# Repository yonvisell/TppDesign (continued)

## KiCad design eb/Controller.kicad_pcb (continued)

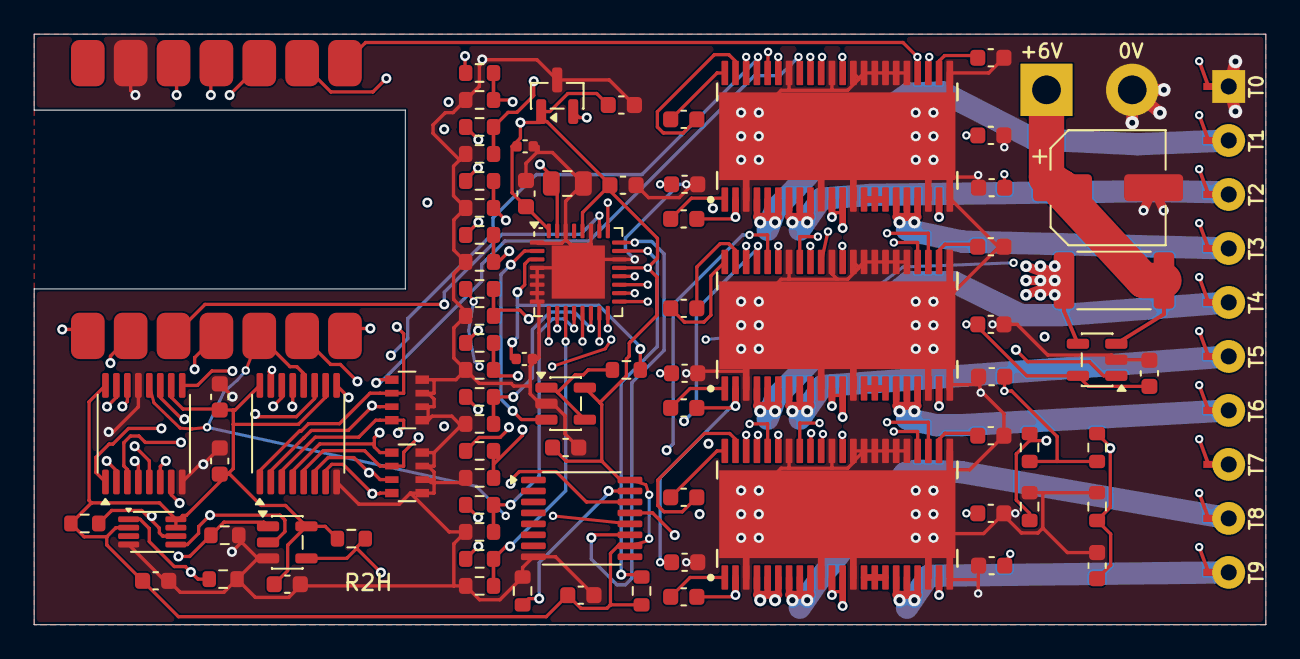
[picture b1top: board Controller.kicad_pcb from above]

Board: 4 copper layers, 73.0 x 35.0 mm, 82 parts (0 on the bottom side), 85 nets.

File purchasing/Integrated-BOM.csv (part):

group,ref,item,supplier,identity,purchase_unit,low,high,first,repeat,second,existing_eb,basis,source,first_low,first_high,repeat_low,repeat_high,second_low,second_high,existing_eb_low,existing_eb_high
Display / tooling,H01,"Four-layer display board, 0.80 mm FR-4",JLCPCB,R2J display PCB Gerbers and drill files,5 bare boards,35.0,115.0,1,0.2,0,1,"Allowance for five boards and precision routing on a removable rail panel. Confirm total aperture contour position to copper and datums, inside radius and inner 1 oz layers. One of five bare display boards.",https://jlcpcb.com/capabilities/pcb-capabilities/,35.0,115.0,7.0,23.0,0.0,0.0,35.0,115.0
Display / tooling,H02,Bare annealed 0.127 mm C110 copper,Trinity Brand Industries,6CPR12-5,"1 sheet, 6 × 12 in",14.96,14.96,1,0.041666666666666664,0,1,"Catalog unit, ASTM B152. Hand-trim identical 10 mm-wide tab outlines and perforate the upper foil with nine 0.600 mm holes. 24 copper pairs per sheet after offcuts and witnesses.",https://www.trinitybrand.com/item/copper/copper-1/6cpr12-5,14.96,14.96,0.6233333333333333,0.6233333333333333,0.0,0.0,14.96,14.96
Display / tooling,H03a,Plain 0.0254 mm Kapton HN dielectric,CS Hyde,18-1F-12x12,"1 sheet, 12 × 12 in",10.9,10.9,1,0.02,0,1,Catalog unit. L02/L03 and L11/L12 protect the two tab roots. Cut three 0.60 × 1.48 mm wire-tail retainers from upper-liner offcuts. 50 display sets per plain HN sheet. Two blanks per set; K1–K3 use offcuts.,https://catalog.cshyde.com/viewitems/films/kapton-polyimide-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,10.9,10.9,0.218,0.218,0.0,0.0,10.9,10.9
Display / tooling,H03c,Plain 0.1016 mm polyimide spacer sheet,CS Hyde,18-4F-P,"1 ft, 20 in wide",50.87,50.87,1,0.00625,0,1,Catalog unit. Use solid 4 mil polyimide. Measure installed spacer and free gasket thickness. 160 compression spacers per 20 x 12 inch PI sheet.,https://cshyde.com/item/films/thick-polyimide-film/4mil-poly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,50.87,50.87,0.3179375,0.3179375,0.0,0.0,50.87,50.87
Display / tooling,H03d,"Acrylic transfer adhesive, two release liners",CS Hyde / 3M,3M-467MP-12x12,"1 sheet, 12 × 12 in",5.76,5.76,1,0.0625,0,1,"Catalog unit, 0.0584 mm dry. Prelaminate PI before blade cutting and retain the release liner. Bore L11/L12 to 0.425 mm after registering to L13. 16 sets of six transfer adhesive patterns per sheet.",https://cshyde.com/item/3m-products/3m-adhesive-transfer-tap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,5.76,5.76,0.36,0.36,0.0,0.0,5.76,5.76
Display / tooling,H04,Rigid 0.40 mm bare FR-4 aperture cap,JLCPCB,R2J aperture cap Gerber and drill,5 bare caps,12.0,55.0,1,0.2,0,1,"Allowance. Manual review for thin FR-4 with no metal, solder mask or marks on the finished article. Confirm plotted apertures, tolerance and bonding surfaces. One of five aperture caps.",https://jlcpcb.com/capabilities/pcb-capabilities/,12.0,55.0,2.4000000000000004,11.0,0.0,0.0,12.0,55.0
Display / tooling,H05,"Silicone/acrylic face bond, 0.14 mm",Guardia Industries / 3M,"3M 9731 cut sheet, listing 196227895184","1 sheet, 10 × 10 in",12.0,12.0,1,0.016666666666666666,0,1,"Marketplace cut sheet. Verify lot, age, liners and witness adhesion on the actual cap and silicone. Full-roll alternative adds $230 before tax. 60 face bonds per 10 x 10 inch sheet after witnesses.",https://www.ebay.com/itm/196227895184,12.0,12.0,0.2,0.2,0.0,0.0,12.0,12.0
Display / tooling,H06,Plain 0.010 in 35A silicone,McMaster-Carr,86435K31,"1 sheet, 12 × 12 in",25.0,70.0,1,0.02,0,1,SKU and size in catalog. Account price and ship date unconfirmed. Cut both bare silicone parts in the lab. 50 gasket and diaphragm pairs per sheet after trials.,https://www.mcmaster.com/products/rubber/color~cream/,25.0,70.0,0.5,1.4000000000000001,0.0,0.0,25.0,70.0
Display / tooling,H07,Bare Ni80Cr20 AWG 48 heater wire,KP Wire,N80_500_SPOOL_48g,"1 spool, 500 ft",25.2,25.2,1,0.004330708661417323,0,1,Selected gauge listed as purchasable. Allow 55 mm per strand cut. Four-strand build uses at most twelve 55 mm cuts.,https://kpwire.com/remote/v1/product-attributes/133?attribut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,25.2,25.2,0.10913385826771653,0.10913385826771653,0.0,0.0,25.2,25.2
Display / tooling,H08,"26 AWG, 19/38 thin-wall PTFE tap leads",WireMasters,M16878/6-BDE-9,24 ft cut length,9.6,9.6,1,0.4101049868766404,0,1,Unit price $0.40/ft. The lot supplies two ten-lead harnesses and 1.32 m total cutting margin. Identify both ends before assembly. 3.0 m of leads used from the 24 ft first purchase.,https://www.wiremasters.com/product/m16878-6-bde-9,9.6,9.6,3.9370078740157473,3.9370078740157473,0.0,0.0,9.6,9.6
Display / tooling,H09a,Winding-tool base PCB,JLCPCB,R2J winding base fabrication CAM,5 bare boards,5.0,25.0,1,0,0,1,Bare-board and relief machining allowance. Reusable base PCB.,https://jlcpcb.com/capabilities/pcb-capabilities/,5.0,25.0,0.0,0.0,0.0,0.0,5.0,25.0
Display / tooling,H09b,Adjustable winding frame PCB,JLCPCB,R2J winding frame fabrication CAM,5 bare boards,8.0,35.0,1,0,0,1,"Allowance for bare FR-4 plate with 24 guides, two clamp slots and a display clearance window. Reusable frame PCB.",https://jlcpcb.com/capabilities/pcb-capabilities/,8.0,35.0,0.0,0.0,0.0,0.0,8.0,35.0
Display / tooling,H10,Straight 0.30 mm steel winding-guide stock,Vermont Gage,"112200300, Class ZZ minus, 2 in","4 blanks, 2 in each",21.0,21.0,1,0,0,1,Maker catalog $5.25 per blank. Four 50.8 mm lengths yield 28 nominal 6 mm sections allowing cutting kerf. Confirm seller stock. Winding guides stay with the tooling.,https://vermontgage.com/assets/catalogs/2025-VG-Catalog/f37c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,21.0,21.0,0.0,0.0,0.0,0.0,21.0,21.0
Display / tooling,H11,Straight 0.45 mm steel registration stock,Vermont Gage,"112400450, Class ZZ minus, 2 in","1 blank, 2 in",5.25,5.25,1,0,0,1,Maker catalog $5.25 per blank. One 50.8 mm length yields seven nominal 6 mm sections allowing cutting kerf. Confirm seller stock. Registration pins stay with the tooling.,https://vermontgage.com/assets/catalogs/2025-VG-Catalog/f37c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,5.25,5.25,0.0,0.0,0.0,0.0,5.25,5.25
Display / tooling,H12,"M2 clamps, caul and shop consumables",Owner shop,"M2 hardware, caul blank, epoxy, strain relief, labels, blades and bits",1 shop lot,7.0,30.0,1,0.1,0,1,"Shop allowance for a supported precision drill or punch, sacrificial backer, M2 clamps and supplies. Assumes existing microscope, adjustable stage, solder tools and Rayjet. Optional thermal-joint tooling and qualification are outside the flat-head budget. Estimated 10% repeat usage for labels and consumables. M2 hardware is reused.",Shop allowance,7.0,30.0,0.7000000000000001,3.0,0.0,0.0,7.0,30.0
Driver components,A1,XIAO ESP32-C6,Seeed via JLCPCB,113991254 / C27675191,1 component,7.6389,7.6389,2,1,0,0,1 per board. Two boards plus purchase minimum or attrition. Catalog stock at the saved lookup: 96.,https://jlcpcb.com/partdetail/C27675191,15.2778,15.2778,7.6389,7.6389,0.0,0.0,0.0,0.0
Driver components,U6,74LVC1G74,Texas Instruments via JLCPCB,SN74LVC1G74DCUR / C70285,1 component,0.4991,0.4991,5,1,0,0,1 per board. Two boards plus purchase minimum or attrition. Catalog stock at the saved lookup: 3874.,https://jlcpcb.com/partdetail/C70285,2.4955,2.4955,0.4991,0.4991,0.0,0.0,0.0,0.0
Driver components,U7,74LVC1G00,Texas Instruments via JLCPCB,SN74LVC1G00DBVR / C7826,1 component,0.2158,0.2158,6,1,0,0,1 per board. Two boards plus purchase minimum or attrition. Catalog stock at the saved lookup: 13788.,https://jlcpcb.com/partdetail/C7826,1.2948,1.2948,0.2158,0.2158,0.0,0.0,0.0,0.0
Driver components,"C24,C25,C22,C23,C2,C4,C8,C10,C14,C16,C26,C28,C34",100nF,YAGEO via JLCPCB,CC0603KRX7R9BB104 / C14663,1 component,0.0064,0.0064,41,13,0,0,13 per board. Two boards plus purchase minimum or attrition. Catalog stock at the saved lookup: 53069809.,https://jlcpcb.com/partdetail/C14663,0.2624,0.2624,0.08320000000000001,0.08320000000000001,0.0,0.0,0.0,0.0
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
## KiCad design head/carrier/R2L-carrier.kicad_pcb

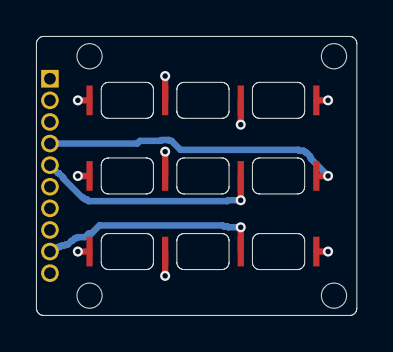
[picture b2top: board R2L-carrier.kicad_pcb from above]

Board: 4 copper layers, 17.8 x 15.5 mm, 17 parts (0 on the bottom side), 10 nets.

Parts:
B10, B11, B12, B13, B20, B21, B22, B23, B30, B31, B32, B33: Shared_pressure_bar
D1, D2, D3, D4: Alignment_NPTH
W1: Direct_solder_individual_wires

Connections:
T0: B10.1, W1.1
T1: B11.1, W1.2
T2: B12.1, W1.3
T3: B13.1, B23.1, W1.4
T4: B22.1, W1.5
T5: B21.1, W1.6
T6: B20.1, B30.1, W1.7
T7: B31.1, W1.8
T8: B32.1, W1.9
T9: B33.1, W1.10

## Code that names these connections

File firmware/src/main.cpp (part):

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
SET_LOOP_TASK_STACK_SIZE(16384);
using namespace tpp;
constexpr int RUN=D1, MISO_ADC=D2,ARM_PIN=D3,LATCH=D4,DIR9=D5,CS=D6,FAULT=D7,SCLK_PIN=D8,Q_ARM=D9,MOSI_PIN=D10;
WiFiUDP udp;Preferences nv;State control;tpp::Server server;
char ap[32],pass[20];int unitID=1;uint32_t headID=1;bool timerReady=false,udpReady=false;
uint64_t usNow(){return uint64_t(esp_timer_get_time());}
bool healthy(){return digitalRead(FAULT)&&digitalRead(Q_ARM);}
bool runHigh(){return gpio_get_level(static_cast<gpio_num_t>(RUN));}
void latch(Pins p){
    uint32_t w=shiftWord(p);digitalWrite(DIR9,(p.hi>>8)&1);digitalWrite(LATCH,LOW);
    SPI.transfer(w>>16);SPI.transfer(w>>8);SPI.transfer(w);
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} storage;
bool armHardware(){
    if(!timerReady||!digitalRead(FAULT)||!hw.readIdle())return false;
    digitalWrite(ARM_PIN,HIGH);delayMicroseconds(3);digitalWrite(ARM_PIN,LOW);return healthy();
}
bool calibrate(float ambient,float r20){
    disarm();return enroll(control,hw,storage,ESP.getEfuseMac(),headID,ambient,r20);
}
void info(){
    Serial.printf("TPP-R2L %s array_label=%lu port=5054 AP=%s key=%s station=%s rail=%.3f Ablank=%.4f cal=%d cold=%d armed=%d fault=%d Tmax=%.1f wires=%d mode=%d\n",
        server.addr,(unsigned long)headID,ap,pass,WiFi.localIP().toString().c_str(),hw.rail,hw.blankA,control.calibrated,control.cold,control.armed,control.fault,control.ceiling,control.wires,int(control.mode));
    if(control.calibrated){Serial.printf("A=%.2f R20=%.5f G=%.5f beta=%.3f gamma=%.3f Rseries ohm row-major",control.cal.ambient,control.cal.r20,control.tuning.g_W_K,control.tuning.beta,control.tuning.gamma);for(float r:control.cal.series)Serial.printf(" %.5f",r);Serial.println();}
}
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            disarm();control.armed=control.calibrated&&control.cold&&!control.fault&&armHardware();info();
        }else if(!strncmp(line,"WIFI ",5)){
            char* sep=strchr(line+5,'\t');if(sep&&sep>line+5&&sep-line-5<=32&&strlen(sep+1)<=63){*sep=0;WiFi.begin(line+5,sep+1);}
        }else Serial.println("ID | UNIT n | ARRAY label | WIRES n | OFF | CAL COLD degC [bundle_ohm_at_ambient] | MODEL G_mW/K beta gamma | COLD | ARM | LIMIT degC | WIFI ssid<TAB>password");
        memset(line,0,sizeof(line));
    }
}
void setup(){
    for(int p:{RUN,LATCH,DIR9,ARM_PIN,SCLK_PIN,MOSI_PIN}){pinMode(p,OUTPUT);digitalWrite(p,LOW);}
    pinMode(CS,OUTPUT);digitalWrite(CS,HIGH);pinMode(FAULT,INPUT);pinMode(Q_ARM,INPUT);
    SPI.begin(SCLK_PIN,MISO_ADC,MOSI_PIN,-1);SPI.beginTransaction(SPISettings(4000000,MSBFIRST,SPI_MODE0));latch({0,0});
    timerReady=rmtInit(RUN,RMT_TX_MODE,RMT_MEM_NUM_BLOCKS_1,1000000)&&rmtSetEOT(RUN,0)&&gpio_input_enable(static_cast<gpio_num_t>(RUN))==ESP_OK;
    Serial.begin(115200);nv.begin("tpp-r2i",false) /* retain setup keys; validate the separate calibration record version */;unitID=std::clamp(int(nv.getUInt("unit",1)),1,999);
    control.wires=int(nv.getUInt("wires",2));
    headID=nv.getUInt("array",1);restoreCalibration(control,storage,ESP.getEfuseMac(),headID);newEpoch();
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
